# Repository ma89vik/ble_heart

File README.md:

# ble_heart

# Pre-Requirements
 * CMake installed

# Building the project
 * Set TOOLCHAIN_PATH to the path to your arm-none-eabi folder if toolchain not in path
 * Set NRF_SDK_PATH to the path to your nrf52 SDK
 * Install python requirements from requirements.txt

# Feature plans
 * Pairing process between two devices
 * Every X ms send advertise
 * Button pressed: set up central scan for adv packets from paired device 
    - If found, connect to device, signal with lights, use RSSI to estimate distance -> brighter light, -> go back to power saving after X sec if no button press
    - Heart shaped led, button press->display on connected device
 * Debug mode:
    - RTT logging   

# TODO
CI:
  * Check app dont overwrite bootloader

App:

Bootloader:
 * Currently unable to download app image

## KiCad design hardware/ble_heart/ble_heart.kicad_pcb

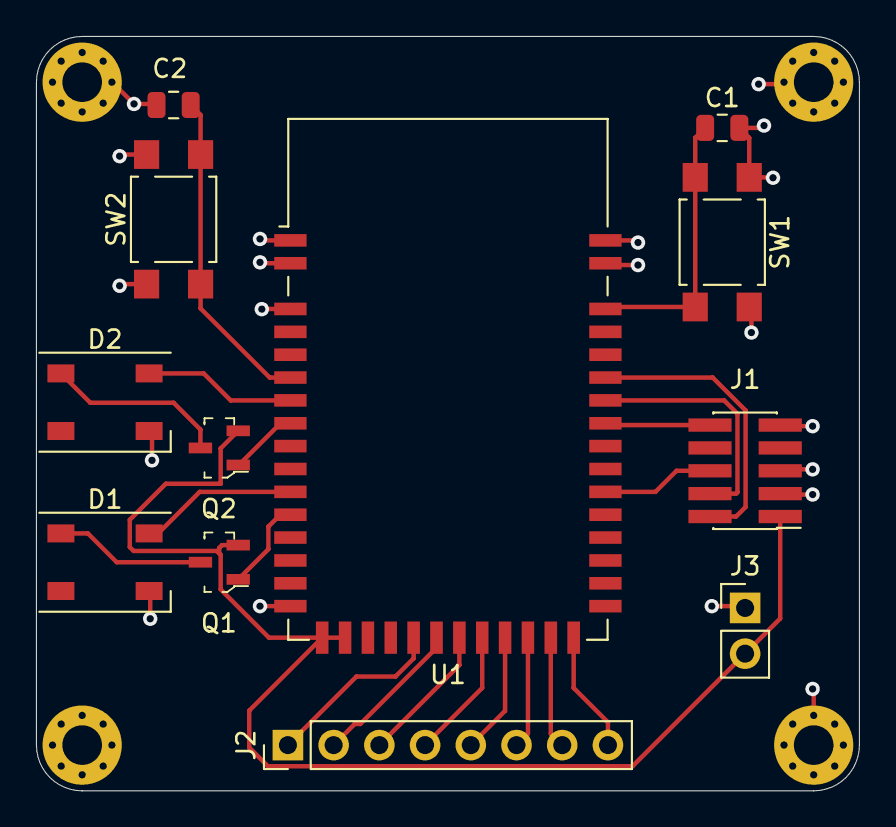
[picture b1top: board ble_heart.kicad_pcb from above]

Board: 2 copper layers, 45.7 x 41.9 mm, 16 parts (0 on the bottom side), 22 nets.

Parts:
C1, C2: C_Small; C_0805_2012Metric
D1, D2: WS2812B; LED_WS2812B_PLCC4_5.0x5.0mm_P3.2mm
H1, H2, H3, H4: MountingHole_Pad; MountingHole_2.2mm_M2_Pad_Via
J1: SWD; PinHeader_2x05_P1.27mm_Vertical_SMD
J2: GPIO; PinHeader_1x08_P2.54mm_Vertical
J3: PWR; PinHeader_1x02_P2.54mm_Vertical
Q1, Q2: AO3401A; SOT-23-3
SW1, SW2: SW_Push; SW_SPST_TL3305A
U1: E73-2G4M04S-52832; E73-2G4M04S

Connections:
+3V3: J1.1, J3.2, Q1.2, Q2.2, U1.16, U1.17
BUTTON_1: C1.1, SW1.2, U1.41
BUTTON_2: C2.1, SW2.2, U1.5
GND: C1.2, C2.2, D1.3, D2.3, H1.1, H2.1, H3.1, H4.1, J1.3, J1.5, J1.9, J3.1, SW1.1, SW2.1, U1.0, U1.1, U1.2, U1.15, U1.42, U1.43
unnamed: D1.1, Q1.3
unnamed: D2.1, Q2.3
unnamed: J2.1, U1.20
unnamed: J2.2, U1.21
unnamed: J2.3, U1.22
unnamed: J2.4, U1.23
unnamed: J2.5, U1.24
unnamed: J2.6, U1.25
unnamed: J2.7, U1.26
unnamed: J2.8, U1.27
RGB_1_CTRL: D1.4, U1.10
RGB_1_PWR: Q1.1, U1.11
RGB_2_CTRL: D2.4, U1.6
RGB_2_PWR: Q2.1, U1.7
RST: J1.10, U1.36
SWD_CLK: J1.4, U1.37
SWD_IO: J1.2, U1.38
SWO: J1.6, U1.33

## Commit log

2021-01-20 Add intial build system frame work
2021-01-21 build: can build and flash example
2021-02-01 build-system: can build example app
2021-02-01 HW: add initial sch
2021-07-15 Finish PCB v1.0
2021-07-15 Add fab files for v1.0
2022-01-21 Can flash and boot simple BLE blink example
2022-01-21 build system: add base meson files
2022-01-23 build system: initial meson framework files
    Can build app with meson.
2022-01-23 add nrf sdk
2022-01-23 build system: add elf 2 bin target
